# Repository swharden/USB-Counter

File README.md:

# USB Counter

This project contains the design files and notes for a USB counter. By populating one of two input paths with components this device can serve as a sensitive frequency counter (with a small-signal amplifier front-end) or a pulse counter (with a simple 50 ohm load at the front-end). Measured frequency is sent to the computer over USB, but can also be displayed on an optional 7-segment display module.

### LED Display

In addition to serial output, this counter can optionally interface a SPI-driven 7-segment display (based on a MAX7219). These display modules are about [$4 on Amazon](https://www.amazon.com/s?k=max7219+segment) and allow this counter to be used without a computer. Note that the LED display and USB output can both be used at the same time.

### USB (Serial) Output

When plugged in to a USB port the counter looks like a serial device. It continuously transmits the count (at 115200 baud) at an update rate which can be customized (commonly 1Hz, 10Hz, and 100Hz.) The output is two numbers: time (in seconds) and the count between the last update and this one. In this example it is measuring a radio frequency signal near 10.139977 MHz

### Precision Frequency Measurement

One advantage of this counter is that it is never reset. Its core is a 32-bit counter, and every gate cycle transmits the current count to the computer over USB. Because every input cycle is measured high precision measurements of frequency over long periods of time are possible. For example, 1000 repeated measurements with a 1Hz gate allows frequency measurement to a precision of 0.01 Hz.

### Internal or External Gating
The microcontroller is capable of generating gate cycles in software. Precision is limited to that of the TCXO used to clock the microcontroller (2.5 PPM). For higher-precision gating a resistor may be lifted and an external gate applied (e.g., 1PPS GPS signal).

### Design and Build Notes

* [Revision 1.0 - schematics and PCB design](/builds/1.0) - first tested 2019-07-26
* [Revision 1.1 - schematics and PCB design](/builds/1.1) - first tested 2019-08-03

### About

This project was created by [Harden Technologies, LLC](http://tech.swharden.com). To inquire about the development special features or customized versions of this hardware or software, contact the author at [SWHarden@gmail.com](mailto:swharden@gmail.com).

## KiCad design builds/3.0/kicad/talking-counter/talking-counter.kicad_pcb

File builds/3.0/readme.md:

# Talking Frequency Counter

This version of the frequency counter uses USB for power (not connectivity) and speaks frequency out loud when a button is pressed. Once finished this project will probably be moved into its own repository.

## Build Notes

* VDDIO2 should be connected to 3.3V (required bodge wire)
* Crystal pads are silly big
* Audio amplifier shutdown should be pulled LOW not HIGH
* Volume knob is wired backwards
* Rename header 3.3v to VCC
* Button is wired incorrectly (always grounded)
* Move header closer to the edge or use different system
* Don't use port C for LEDs or button

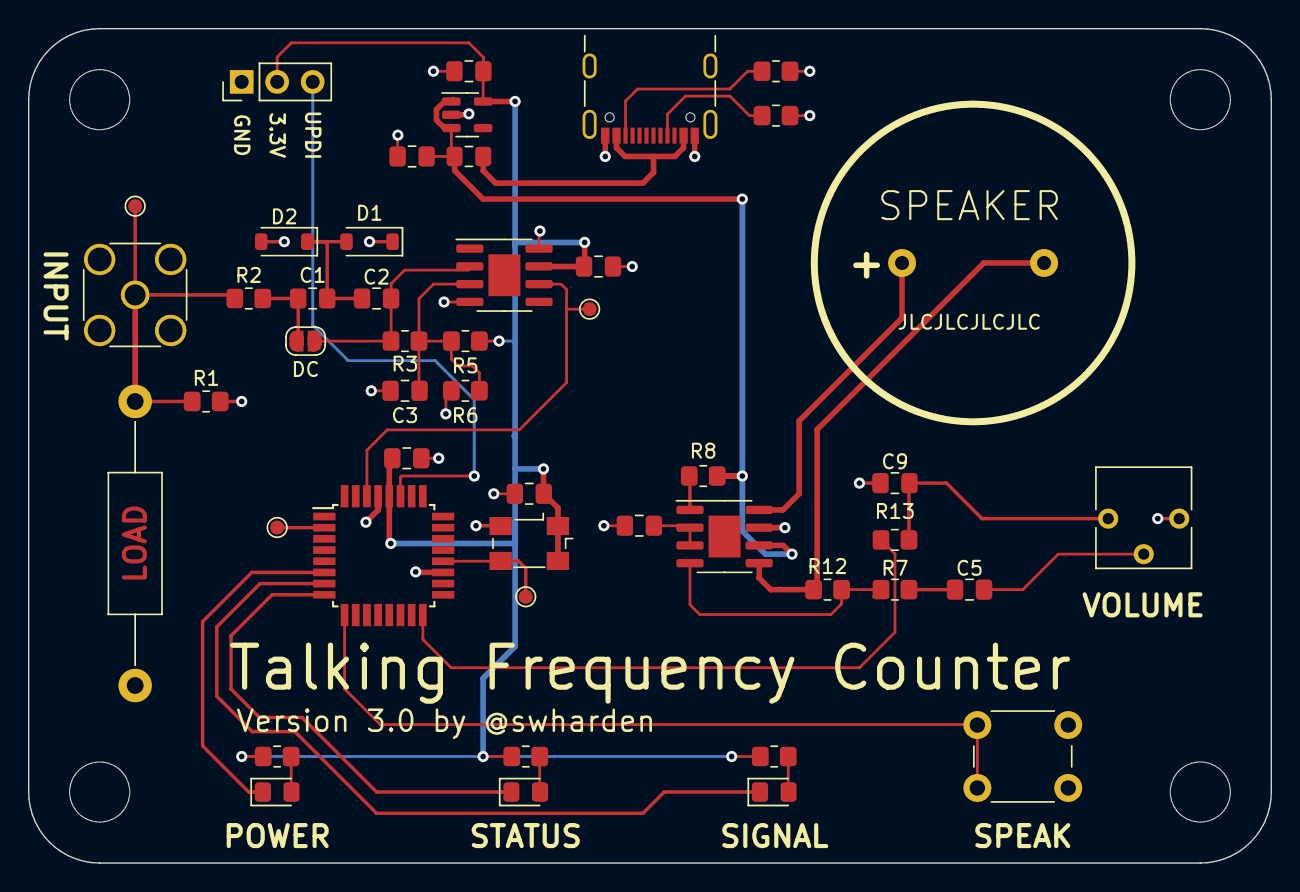
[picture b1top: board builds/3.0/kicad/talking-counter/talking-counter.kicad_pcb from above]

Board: 2 copper layers, 88.9 x 59.7 mm, 48 parts (0 on the bottom side), 31 nets.

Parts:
C1, C2, C3, C4, C5, C6, C7, C8, C9, C10, C11: .1u; C_0805_2012Metric_Pad1.18x1.45mm_HandSolder
D1, D2: D; D_SOD-123
D3: SIGNAL; LED_0805_2012Metric_Pad1.15x1.40mm_HandSolder
D4: STATUS; LED_0805_2012Metric_Pad1.15x1.40mm_HandSolder
D6: POWER; LED_0805_2012Metric_Pad1.15x1.40mm_HandSolder
FB2: Ferrite; L_0805_2012Metric_Pad1.15x1.40mm_HandSolder
IC1: TLV3501AIDR; SOIC-8-1EP_3.9x4.9mm_P1.27mm_EP2.29x3mm
IC2: LM4862MX_NOPB; SOIC-8-1EP_3.9x4.9mm_P1.27mm_EP2.29x3mm
J1: Conn_Coaxial; SMA_Amphenol_132134_Vertical
J2: PROG; PinHeader_1x03_P2.54mm_Vertical
J3: USB_C_Receptacle_PowerOnly_6P; USB_C_Receptacle_GCT_USB4105-xx-A_16P_TopMnt_Horizontal
JP1: DC_INPUT; SolderJumper-2_P1.3mm_Open_RoundedPad1.0x1.5mm
LS1: Speaker; speaker SM231508
R1, R3: 100k; R_0805_2012Metric_Pad1.20x1.40mm_HandSolder
R2, R7: 1k; R_0805_2012Metric_Pad1.20x1.40mm_HandSolder
R4, R5, R6, R8, R9, R13, R16: 10k; R_0805_2012Metric_Pad1.20x1.40mm_HandSolder
R10, R11: 5.1k; R_0805_2012Metric_Pad1.20x1.40mm_HandSolder
R12: 47k; R_0805_2012Metric_Pad1.20x1.40mm_HandSolder
RV1: R_VOL; Potentiometer_Vishay_T73YP_Vertical
R_LOAD1: 50; R_Axial_DIN0411_L9.9mm_D3.6mm_P20.32mm_Horizontal
SW1: SPEAK; SW_PUSH_6mm_H5mm
TP1: AMP_OUT; TestPoint_Pad_D1.0mm
TP2: 10MHz; TestPoint_Pad_D1.0mm
TP3: SIG_IN; TestPoint_Pad_D1.0mm
TP4: MCU_TX; TestPoint_Pad_D1.0mm
U2: AP2112K-3.3; SOT-23-5
U3: AVR64DD32; TQFP-32_7x7mm_P0.8mm
U4: FT5HV; Oscillator_SMD_Fox_FT5H_5.0x3.2mm

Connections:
+3.3V: C4.2, C7.2, C8.2, C11.2, IC1.7 (V+), J2.2, R4.2, R5.2, R9.2, R16.2, U2.5 (VOUT), U3.28 (VDD), U4.1 (VC), U4.4 (VDD)
+5V: C10.2, FB2.2, IC2.6 (VDD), R8.1, U2.1 (VIN), U2.3 (EN)
COMP_OUT: IC1.6 (OUT), TP1.1, U3.30 (PA0)
DAC: C9.2, R13.2, RV1.1
GND: C3.2, C4.1, C6.2, C7.1, C8.1, C9.1, C10.1, C11.1, D1.1 (K), D2.2 (A), IC1.4 (V-), IC1.8 (SHDN), IC2.7 (GND), J1.2 (Ext), J2.1, J3.A1, J3.A12 (GND), R1.2, R6.1, R10.2, R11.2, RV1.3, R_LOAD1.2, SW1.1, SW1.2, U2.2 (GND), U3.19 (GND), U3.29 (GND), U4.2 (GND)
LED1: D6.1 (K), U3.6 (PC0)
LED2: D3.1 (K), U3.7 (PC1)
LED3: D4.1 (K), U3.8 (PC2)
unnamed: C5.1, R7.2
unnamed: C5.2, RV1.2
unnamed: C1.1, C2.2, D1.2 (A), D2.1 (K)
unnamed: D3.2 (A), R4.1
unnamed: D4.2 (A), R9.1
unnamed: D6.2 (A), R16.1
unnamed: FB2.1, J3.A4, J3.A9 (VBUS)
unnamed: C3.1, IC1.3 (+IN), R3.1, R5.1, R6.2
unnamed: C2.1, IC1.2 (-IN), JP1.2 (B), R3.2
unnamed: C6.1, IC2.2 (BYPASS), IC2.3 (+IN)
unnamed: IC2.4 (-IN), R7.1, R12.2
unnamed: IC2.1 (SHUTDOWN), R8.2
unnamed: IC2.5 (VO1), LS1.2, R12.1
unnamed: IC2.8 (VO2), LS1.1
unnamed: J1.1 (In), R1.1, R2.1, R_LOAD1.1, TP3.1
unnamed: J2.3, U3.27 (UPDI)
unnamed: J3.A5 (CC1), R11.1
unnamed: J3.B5 (CC2), R10.1
unnamed: C1.2, JP1.1 (A), R2.2
unnamed: TP4.1, U3.2 (PA4)
unnamed: SW1.1, SW1.2, U3.9 (PC3)
unnamed: R13.1, U3.16 (PD6)
unnamed: TP2.1, U3.20 (XTAL32K1/PF0), U4.3 (OUT)

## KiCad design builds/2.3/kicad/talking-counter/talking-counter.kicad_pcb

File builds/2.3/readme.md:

# Talking Frequency Counter

This folder contains design notes for a ***talking frequency counter*** designed to help visually impaired radio operators to know what frequency they are transmitting on by speaking the frequency out loud when a button is pressed. This design uses a high-speed analog comparator to amplify signals on the frontend, measures them directly with a microcontroller, sends that data to a PC using a USB serial adapter, and also says the frequency out loud using a speaker.

> **⚠️ WARNING:** This is a work in progress. This board design has some errors which will be corrected in a future build.

## Components
* **AP2112K-3.3TRG1** 600 mA 3.3V LDO regulator ([$0.35 from Mouser](https://www.mouser.com/ProductDetail/Diodes-Incorporated/AP2112K-3.3TRG1?qs=x6A8l6qLYDDPYHosCdzh%2FA%3D%3D))
* **AVR64DD32** 8-bit microcontroller ([$1.51 on Mouser](https://www.mouser.com/ProductDetail/Microchip-Technology/AVR64DD32-I-PT?qs=tlsG%2FOw5FFjuwvYsegdIqg%3D%3D))
* **Oscillator** 10 MHz oscillator, 3.3V, ±2.5 ppm ([$1.89 on Mouser](https://www.mouser.com/ProductDetail/ECS/ECS-TXO-2016-33-100-TR?qs=PzGy0jfpSMvd6OxkHIkpfg%3D%3D))
* **TLV3501** high speed analog comparator ([$3.06 on Mouser](https://www.mouser.com/ProductDetail/Texas-Instruments/TLV3501AIDR?qs=m96fseALk3U7ir0PfDMQ%252BA%3D%3D))
* **LM4862** audio amplifier ([$1.21 on Mouser](https://www.mouser.com/ProductDetail/Texas-Instruments/LM4862MX-NOPB?qs=QbsRYf82W3HZp12WHQE14A%3D%3D))
* **FT231** USB Serial Adapter ([$2.33 on Mouser](https://www.mouser.com/ProductDetail/FTDI/FT231XS-R?qs=Gp1Yz1mis3WduRPsgrTbtg%3D%3D))
* **Diode** 100V 4A 4ns recovery ([$0.13 on Mouser](https://www.mouser.com/ProductDetail/Panjit/1N4148W_R1_00001?qs=sPbYRqrBIVnqVztCqPNVrw%3D%3D))
* **Speaker** 8Ω 300 mW ([$2.09 on Mouser](https://www.mouser.com/ProductDetail/DB-Unlimited/SM231508-1?qs=t9M3m0YJX4Ng139DBuQXjw%3D%3D))
* **USB Connector** type B micro ([$0.46 on Mouser](https://www.mouser.com/ProductDetail/Amphenol-FCI/10118193-0001LF?qs=Ywefl8B65e63Nsqd%252B8HZaQ%3D%3D))
* **USB Connector (next time)** use USBC ([$0.80 on Mouser](https://www.mouser.com/ProductDetail/GCT/USB4105-GF-A?qs=KUoIvG%2F9IlY%2FMLlBMpStpA%3D%3D))
* **0802 Components** are purchased in bulk and essentially free
* **Bumpers** for raising the PCB ([Bumpon SJ5076 from eBay](https://www.mouser.com/datasheet/2/1/Bumpon%20Molded%20Shapes%20Colored%20and%20Clear%20Series%20TDS-845047.pdf))

_Approximately $13 total_

## Schematic

## Preview Render

## Resources

* [100 MHz frequency counter](https://www.electronics-lab.com/project/100mhz-frequency-counter-with-pic16f628a-2/) (designed by Hristo) uses the TLV3501 for its frontend

* [Frequency Measurement with Modern AVR Microcontrollers](https://swharden.com/blog/2023-08-31-avr-dd-frequency-counter/)

* [Play Audio from SPI Flash with a Microcontroller](https://swharden.com/blog/2023-08-26-spi-flash-audio/)

* [Speaking Numbers with a Microcontroller](https://swharden.com/blog/2023-08-19-speaking-microcontroller/)

## Photo

Oof that's a lot of bodges

## Notes During the Build
* PCB edges should be rounded
* Green LEDs should have 47k resistors (not 10k)
* USB lines are incorrect. They should be:
  * 1. VCC
  * 2. ?
  * 3. ?
  * 4. ID (nc)
  * 5. GND
* Need to order more .1 µF caps
* Speaker holes should be bigger
* Volume knob holes should be bigger
* Volume knob polarity should be reversed
* Label programmer pins
* Amplifier shutdown pin should be grounded (not tied to VCC)
* Amplifier resistors should be R12=47k and R7=1k
* The button is wired wrong. Bottom right pin should be grounded.
* Test points should be labeled.
* Add a test point for comparator input and output.
* Ground screw holes.
* Omit RX led (only TX needed)
* Use smaller volume knob and move it away from the button
* Speaker hides power LED
* Move prog header to edge of board
* The load resistor "optional" label is floating beneath the RX/TX leds
* Omit C14 and replace R17 with a 1k resistor
* Use green LEDs everywhere
* Fix the double-press issue
* RF front-end: use a dual diode
* RF front-end: don't tap COMP_OUT with a LED (do that in software)
* Just add TX test pad (not FTDI chip)
* Load comparator output
* Jumper to bypass AC coupling on input

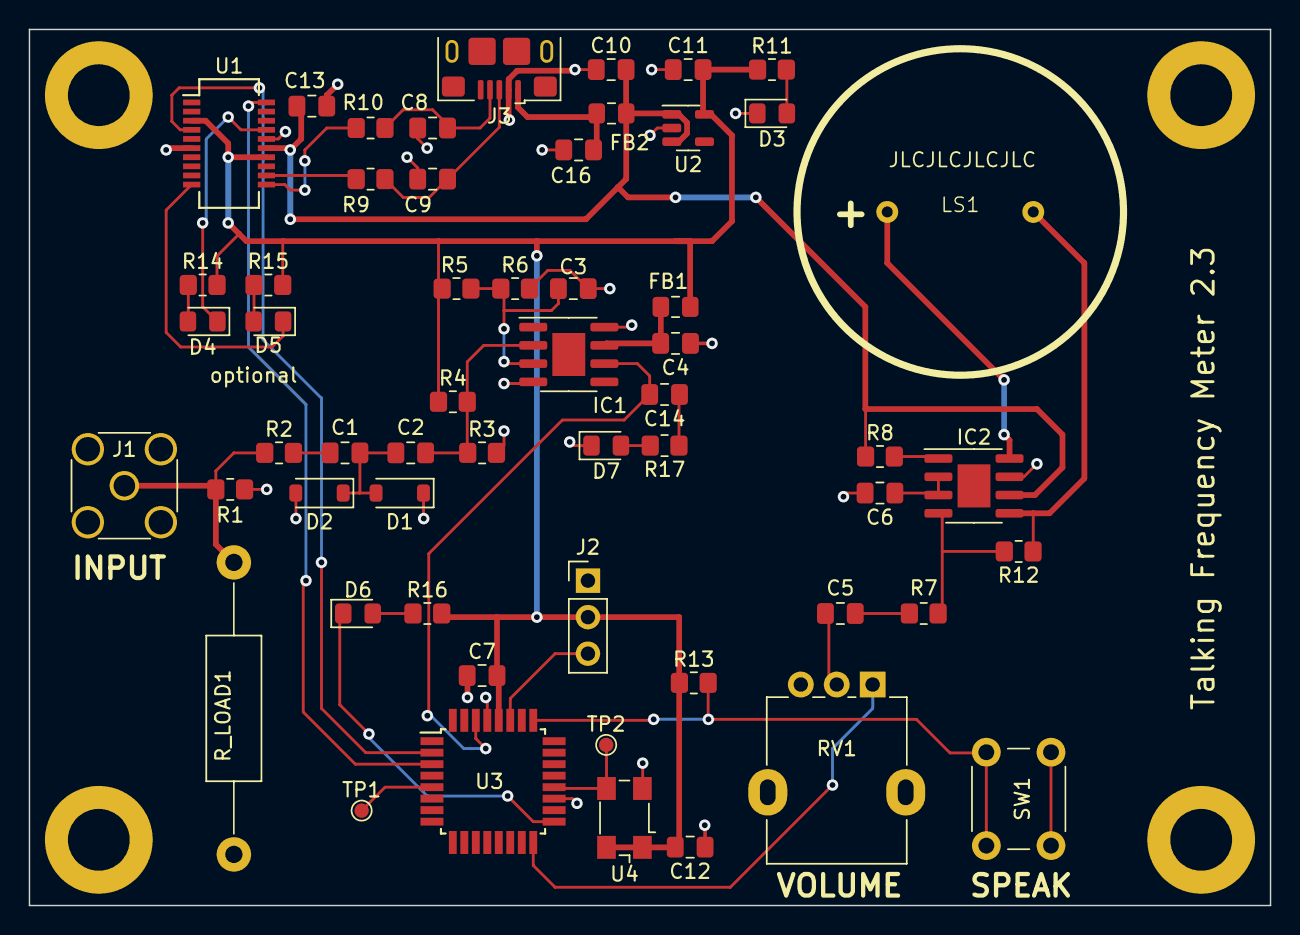
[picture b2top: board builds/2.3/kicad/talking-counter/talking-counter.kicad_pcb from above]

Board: 2 copper layers, 86.4 x 61.0 mm, 60 parts (0 on the bottom side), 38 nets.

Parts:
C1, C2, C3, C4, C5, C6, C7, C10, C11, C12, C13, C14, C16: .1u; C_0805_2012Metric_Pad1.18x1.45mm_HandSolder
C8, C9: 47p; C_0805_2012Metric_Pad1.18x1.45mm_HandSolder
D1, D2: D; D_SOD-123
D3: LED_PWR; LED_0805_2012Metric_Pad1.15x1.40mm_HandSolder
D4: RX_LED; LED_0805_2012Metric_Pad1.15x1.40mm_HandSolder
D5: TX_LED; LED_0805_2012Metric_Pad1.15x1.40mm_HandSolder
D6: LED_STATUS; LED_0805_2012Metric_Pad1.15x1.40mm_HandSolder
D7: LED_SIG; LED_0805_2012Metric_Pad1.15x1.40mm_HandSolder
FB1, FB2: Ferrite; L_0805_2012Metric_Pad1.15x1.40mm_HandSolder
H1, H2, H3, H4: MountingHole; MountingHole_4.3mm_M4_DIN965_Pad
IC1: TLV3501AIDR; SOIC-8-1EP_3.9x4.9mm_P1.27mm_EP2.29x3mm
IC2: LM4862MX_NOPB; SOIC-8-1EP_3.9x4.9mm_P1.27mm_EP2.29x3mm
J1: Conn_Coaxial; SMA_Amphenol_132134_Vertical
J2: PROG; PinHeader_1x03_P2.54mm_Vertical
J3: UJ2-MIBH-G-SMT-TR; USB_Micro-B_Amphenol_10118193-0001LF_Horizontal
LS1: Speaker; speaker SM231508
R1: 100k; R_0805_2012Metric_Pad1.20x1.40mm_HandSolder
R2: 1k; R_0805_2012Metric_Pad1.20x1.40mm_HandSolder
R3, R4, R5, R6, R7, R8, R11, R12, R13, R14, R15, R16, R17: 10k; R_0805_2012Metric_Pad1.20x1.40mm_HandSolder
R9, R10: 27; R_0805_2012Metric_Pad1.20x1.40mm_HandSolder
RV1: R_VOL; Potentiometer_Alpha_RD901F-40-00D_Single_Vertical
R_LOAD1: 50; R_Axial_DIN0411_L9.9mm_D3.6mm_P20.32mm_Horizontal
SW1: SW_MEC_5E; SW_PUSH_6mm_H5mm
TP1: CKOUT; TestPoint_Pad_D1.0mm
TP2: 10MHz; TestPoint_Pad_D1.0mm
U1: FT231XS; SSOP-20_3.9x8.7mm_P0.635mm
U2: AP2112K-3.3; SOT-23-5
U3: AVR64DD32; TQFP-32_7x7mm_P0.8mm
U4: FT5HV; Oscillator_SMD_Fox_FT5H_5.0x3.2mm

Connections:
+5V: C10.2, C13.2, FB2.1, IC2.6 (VDD), R8.1, U1.15 (VCC), U2.1 (VIN), U2.3 (EN)
COMP_OUT: C14.2, IC1.6 (OUT), U3.30 (PA0)
DAC: RV1.1, U3.16 (PD6)
GND: C3.2, C4.1, C6.2, C7.1, C8.2, C9.1, C10.1, C11.1, C12.1, C13.1, C16.1, D1.1 (K), D2.2 (A), D3.1 (K), D7.1 (K), IC1.4 (V-), IC1.8 (SHDN), IC2.7 (GND), J1.2 (Ext), J2.1, J3.2, R1.2, R3.2, R6.1, RV1.3, R_LOAD1.2, U1.6 (GND), U1.16 (GND), U2.2 (GND), U3.19 (GND), U3.29 (GND), U4.2 (GND)
MCU_RX: U1.20 (TXD), U3.3 (PA5)
MCU_TX: U1.4 (RXD), U3.2 (PA4)
unnamed: C1.2, R2.2
unnamed: C5.1, R7.2
unnamed: C5.2, RV1.2
unnamed: C8.1, J3.4, R10.2
unnamed: C9.2, J3.3, R9.1
unnamed: C14.1, R17.1
unnamed: C16.2, FB2.2, J3.1
unnamed: C1.1, C2.2, D1.2 (A), D2.1 (K)
unnamed: D3.2 (A), R11.2
unnamed: D4.2 (A), R14.1
unnamed: D4.1 (K), U1.17 (CBUS1)
unnamed: D5.2 (A), R15.1
unnamed: D5.1 (K), U1.10 (CBUS2)
unnamed: D6.2 (A), R16.1
unnamed: D6.1 (K), U3.17 (VREFA/PD7)
unnamed: D7.2 (A), R17.2
unnamed: C3.1, IC1.3 (+IN), R5.1, R6.2
unnamed: C2.1, IC1.2 (-IN), R3.1, R4.2
unnamed: C4.2, FB1.2, IC1.7 (V+)
unnamed: C6.1, IC2.2 (BYPASS), IC2.3 (+IN)
unnamed: IC2.4 (-IN), R7.1, R12.2
unnamed: IC2.1 (SHUTDOWN), R8.2
unnamed: IC2.5 (VO1), LS1.2, R12.1
unnamed: IC2.8 (VO2), LS1.1
unnamed: J1.1 (In), R1.1, R2.1, R_LOAD1.1
unnamed: J2.3, U3.27 (UPDI)
unnamed: R9.2, U1.12 (USBDM)
unnamed: R10.1, U1.11 (USBDP)
unnamed: TP1.1, U3.5 (PA7)
unnamed: R13.2, SW1.2, U3.25 (PF5)
unnamed: TP2.1, U3.20 (XTAL32K1/PF0), U4.3 (OUT)
VCC: C7.2, C11.2, C12.2, FB1.1, J2.2, R4.1, R5.2, R11.1, R13.1, R14.2, R15.2, R16.2, U1.3 (VCCIO), U1.14 (~RESET), U2.5 (VOUT), U3.28 (VDD), U4.1 (VC), U4.4 (VDD)

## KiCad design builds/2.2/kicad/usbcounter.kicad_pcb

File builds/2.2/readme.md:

# Version 2.2

## Thoughts

* Make an RF amplifier board separately (perhaps with prescaler)
* Input should be 0-5V TTL
* What makes this unique is no-cycle-lost counting
* Ability to accept a 10 MHz lab reference clock is also a big win

## Build notes
* Red and blue LEDs need 1K resistors
* Green LEDs need 47k resistors
* Capacitors on USB line should be 47pF
* LJCPCB blue silkscreen is ugly and doesn't hold up to heat as well as green
* For the crystal oscillator indicate where the dot goes
* It's annoying to keep rotating the board when hand assembling so lay-out passives horizontally
* Move the board ID under one of the ICs
* Consider horizontally mounted headers and SMA connector to facilitate stacking
* Clamp diodes should be downstream of the input decoupling decapacitors
* External 10MHz clock is going into the wrong pin (32 kHz clock). Clock should go to PA0/PA1 and USART use alternate pins PD4/PD5

## Schematic

## Alternative Frontend Designs

### TLV3501 RF Comparator

### OPA356 RF Opamp

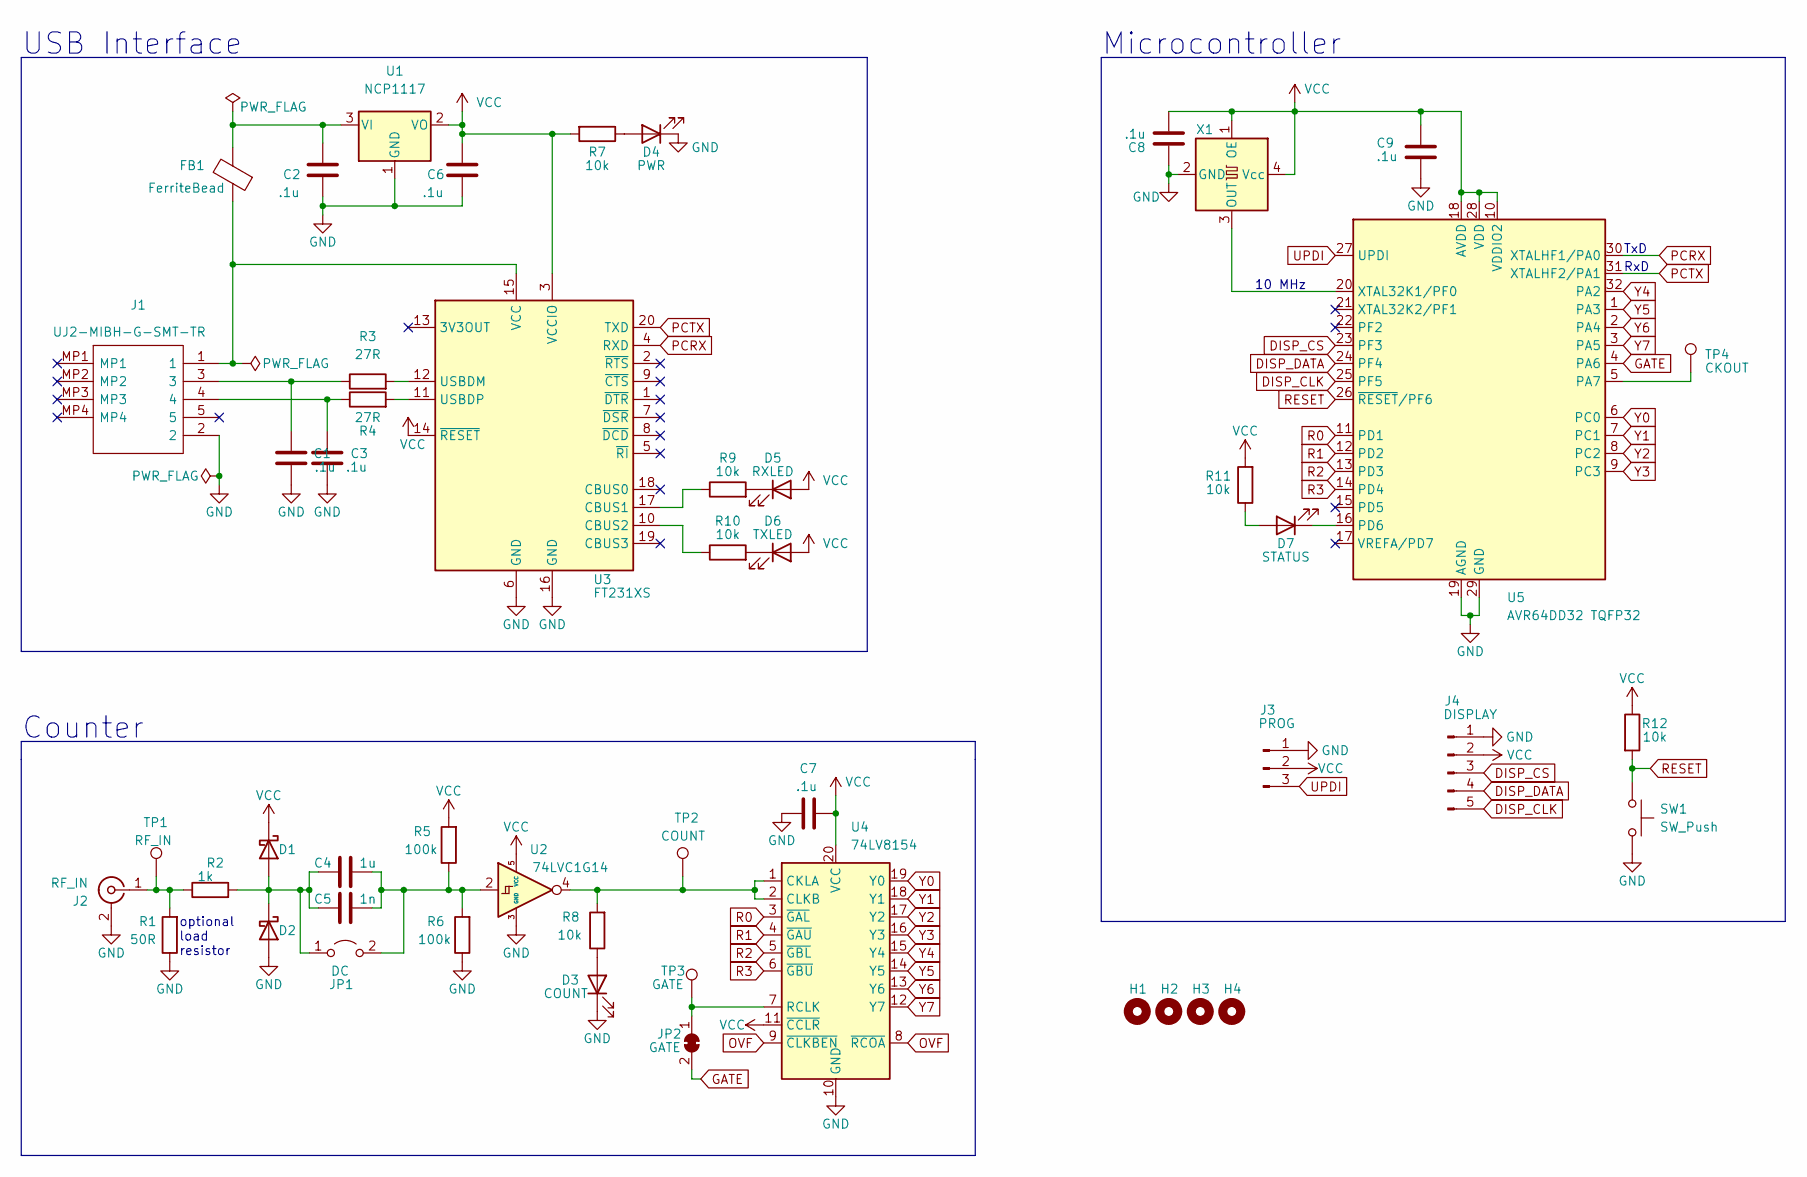
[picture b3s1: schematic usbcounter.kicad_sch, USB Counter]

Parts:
C1, C2, C3, C6, C7, C8, C9: .1u; C_0805_2012Metric_Pad1.18x1.45mm_HandSolder
C4: 1u; C_0805_2012Metric_Pad1.18x1.45mm_HandSolder
C5: 1n; C_0805_2012Metric_Pad1.18x1.45mm_HandSolder
D1, D2: D; LED_0805_2012Metric_Pad1.15x1.40mm_HandSolder
D3: COUNT; LED_0805_2012Metric_Pad1.15x1.40mm_HandSolder
D4: PWR; LED_0805_2012Metric_Pad1.15x1.40mm_HandSolder
D5: RXLED; LED_0805_2012Metric_Pad1.15x1.40mm_HandSolder
D6: TXLED; LED_0805_2012Metric_Pad1.15x1.40mm_HandSolder
D7: STATUS; LED_0805_2012Metric_Pad1.15x1.40mm_HandSolder
FB1: FerriteBead; L_0805_2012Metric_Pad1.15x1.40mm_HandSolder
H1, H2, H3, H4: MountingHole; MountingHole_4.3mm_M4_Pad
J1: UJ2-MIBH-G-SMT-TR; UJ2MIBHGSMTTR; Mouser Part Number 490-UJ2-MIBH-G-SMTTR
J2: RF_IN; SMA_Amphenol_901-144_Vertical
J3: PROG; PinHeader_1x03_P2.54mm_Vertical
J4: DISPLAY; PinHeader_1x05_P2.54mm_Vertical
JP1: DC; SolderJumper-2_P1.3mm_Open_RoundedPad1.0x1.5mm
JP2: GATE; SolderJumper-2_P1.3mm_Bridged_RoundedPad1.0x1.5mm
R1: 50R; R_Axial_DIN0207_L6.3mm_D2.5mm_P7.62mm_Horizontal
R2: 1k; R_0805_2012Metric_Pad1.20x1.40mm_HandSolder
R3, R4: 27R; R_0805_2012Metric_Pad1.20x1.40mm_HandSolder
R5, R6: 100k; R_0805_2012Metric_Pad1.20x1.40mm_HandSolder
R7, R8, R9, R10, R11, R12: 10k; R_0805_2012Metric_Pad1.20x1.40mm_HandSolder
SW1: SW_Push; SW_SPST_TL3342
TP1: RF_IN; TestPoint_Pad_D2.0mm
TP2: COUNT; TestPoint_Pad_D2.0mm
TP3: GATE; TestPoint_Pad_D2.0mm
TP4: CKOUT; TestPoint_Pad_D2.0mm
U1: NCP1117; SOT-223-3_TabPin2
U2: 74LVC1G14; SOT-23-5
U3: FT231XS; SSOP-20_3.9x8.7mm_P0.635mm
U4: 74LV8154; TSSOP-20_4.4x6.5mm_P0.65mm
U5: AVR64DD32 TQFP32; TQFP-32_7x7mm_P0.8mm
X1: TCXO; Oscillator_SMD_SeikoEpson_SG8002CE-4Pin_3.2x2.5mm

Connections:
DISP_CLK: J4.5, U5.25 (PF5)
DISP_CS: J4.3, U5.23 (PF3)
DISP_DATA: J4.4, U5.24 (PF4)
GATE: JP2.2 (B), U5.4 (PA6)
GND: C1.1, C2.1, C3.1, C6.1, C7.1, C8.2, C9.1, D2.2 (A), D3.1 (K), D4.1 (K), J1.2, J2.2 (Ext), J3.1, J4.1, R1.1, R6.1, SW1.2, U1.1 (GND), U2.3 (GND), U3.6 (GND), U3.16 (GND), U4.10 (GND), U5.19 (AGND), U5.29 (GND), X1.2 (GND)
unnamed: C1.2, J1.3, R3.1
unnamed: C2.2, FB1.2, U1.3 (VI)
unnamed: C3.2, J1.4, R4.1
unnamed: C4.1, C5.1, D1.2 (A), D2.1 (K), JP1.1 (A), R2.2
unnamed: C4.2, C5.2, JP1.2 (B), R5.1, R6.2, U2.2
unnamed: D3.2 (A), R8.1
unnamed: D4.2 (A), R7.1
unnamed: D5.1 (K), R9.2
unnamed: D6.1 (K), R10.2
unnamed: FB1.1, J1.1, U3.15 (VCC)
unnamed: J2.1 (In), R1.2, R2.1, TP1.1
unnamed: JP2.1 (A), TP3.1, U4.7 (RCLK)
unnamed: R3.2, U3.12 (USBDM)
unnamed: R4.2, U3.11 (USBDP)
unnamed: R8.2, TP2.1, U2.4, U4.1 (CKLA), U4.2 (CLKB)
unnamed: R9.1, U3.17 (CBUS1)
unnamed: R10.1, U3.10 (CBUS2)
unnamed: D7.2 (A), R11.1
unnamed: TP4.1, U5.5 (PA7)
unnamed: D7.1 (K), U5.16 (PD6)
unnamed: U5.20 (XTAL32K1/PF0), X1.3 (OUT)
OVF: U4.8 (~RCOA), U4.9 (~CLKBEN)
PCRX: U3.4 (RXD), U5.30 (XTALHF1/PA0)
PCTX: U3.20 (TXD), U5.31 (XTALHF2/PA1)
R0: U4.3 (~GAL), U5.11 (PD1)
R1: U4.4 (~GAU), U5.12 (PD2)
R2: U4.5 (~GBL), U5.13 (PD3)
R3: U4.6 (~GBU), U5.14 (PD4)
RESET: R12.2, SW1.1, U5.26 (~RESET/PF6)
UPDI: J3.3, U5.27 (UPDI)
VCC: C6.2, C7.2, C8.1, C9.2, D1.1 (K), D5.2 (A), D6.2 (A), J3.2, J4.2, R5.2, R7.2, R11.2, R12.1, U1.2 (VO), U2.5 (VCC), U3.3 (VCCIO), U3.14 (~RESET), U4.11 (~CCLR), U4.20 (VCC), U5.10 (VDDIO2), U5.18 (AVDD), U5.28 (VDD), X1.1 (OE), X1.4 (Vcc)
Y0: U4.19 (Y0), U5.6 (PC0)
Y1: U4.18 (Y1), U5.7 (PC1)
Y2: U4.17 (Y2), U5.8 (PC2)
Y3: U4.16 (Y3), U5.9 (PC3)
Y4: U4.15 (Y4), U5.32 (PA2)
Y5: U4.14 (Y5), U5.1 (PA3)
Y6: U4.13 (Y6), U5.2 (PA4)
Y7: U4.12 (Y7), U5.3 (PA5)

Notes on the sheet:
USB Interface
TxD
10 MHz
Microcontroller
RxD
Counter
optional load resistor

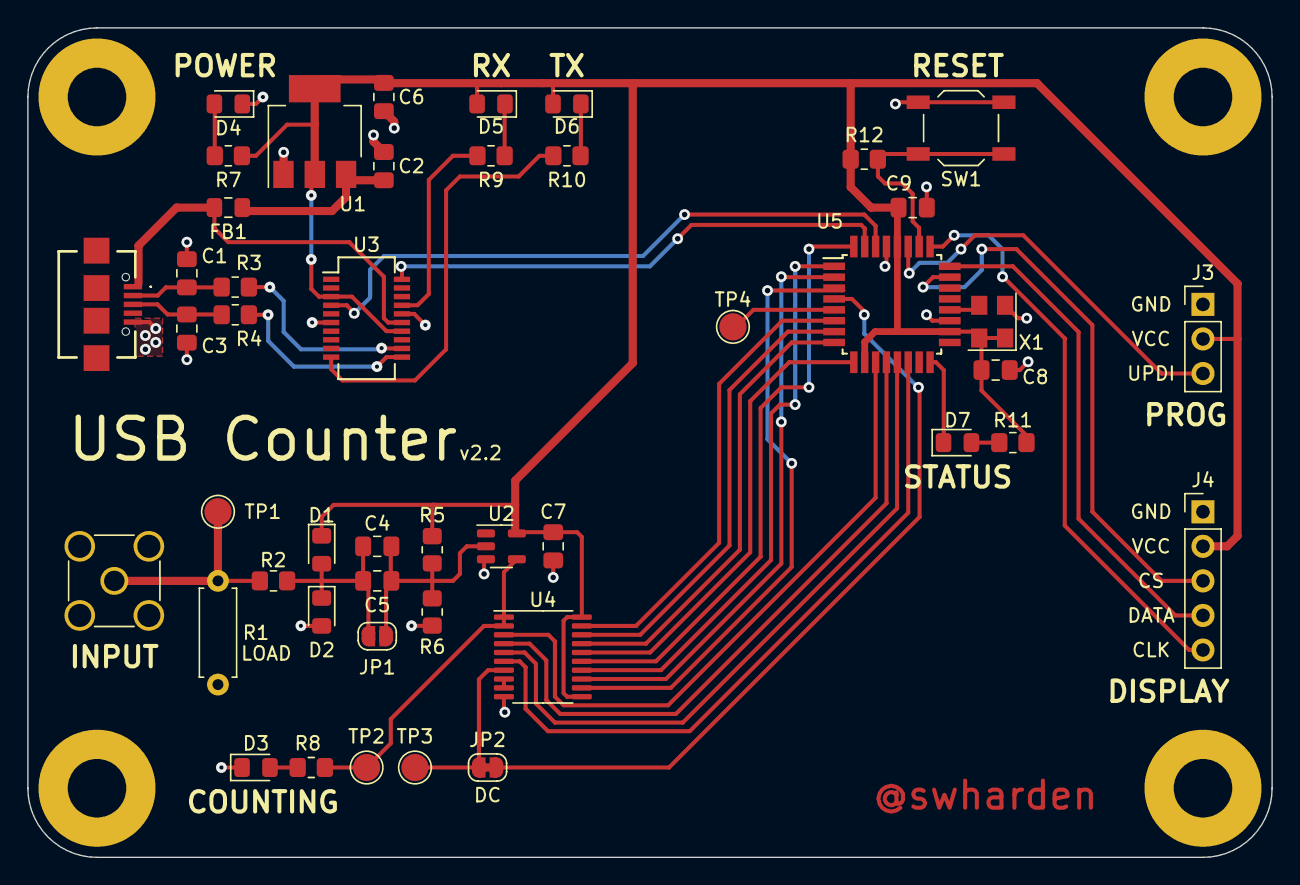
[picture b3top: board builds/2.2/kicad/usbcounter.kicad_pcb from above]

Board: 2 copper layers, 91.4 x 61.0 mm, 50 parts (0 on the bottom side), 44 nets.

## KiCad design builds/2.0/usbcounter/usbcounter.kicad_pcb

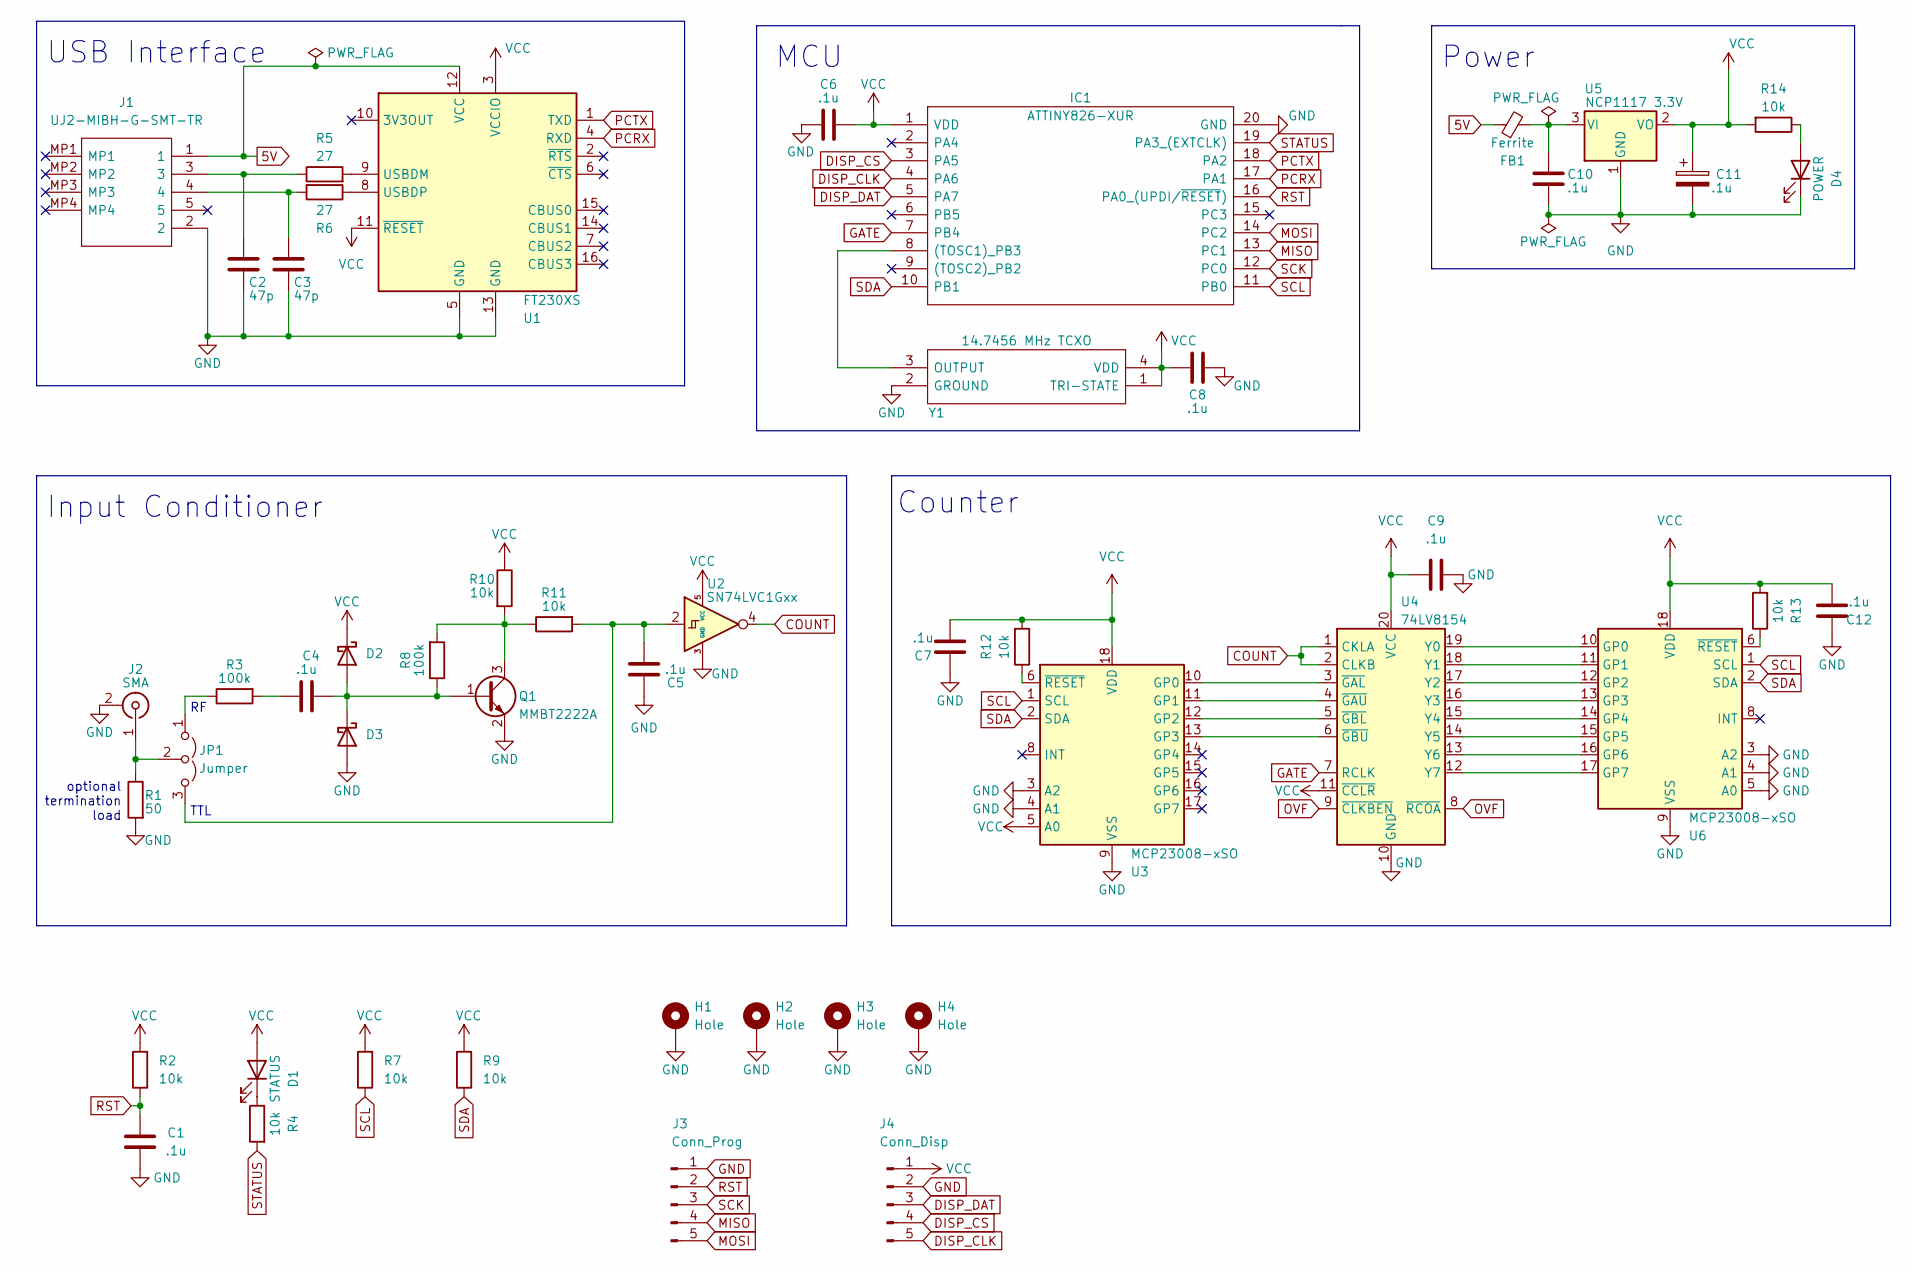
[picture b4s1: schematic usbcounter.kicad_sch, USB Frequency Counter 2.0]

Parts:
C1, C4, C5, C6, C7, C8, C9, C10, C12: .1u; C_0805_2012Metric_Pad1.18x1.45mm_HandSolder
C2, C3: 47p; C_0805_2012Metric_Pad1.18x1.45mm_HandSolder
C11: .1u; CP_EIA-2012-15_AVX-P_Pad1.30x1.05mm_HandSolder
D1: STATUS; LED_0805_2012Metric_Pad1.15x1.40mm_HandSolder
D2, D3: D; D_SOD-323_HandSoldering
D4: POWER; LED_0805_2012Metric_Pad1.15x1.40mm_HandSolder
FB1: Ferrite; L_0805_2012Metric_Pad1.15x1.40mm_HandSolder
H1, H2, H3, H4: Hole; MountingHole_2.2mm_M2_DIN965_Pad
IC1: ATTINY826-XUR; SOP65P780X200-20N; Mouser Part Number 579-ATTINY826-XUR
J1: UJ2-MIBH-G-SMT-TR; UJ2MIBHGSMTTR; Mouser Part Number 490-UJ2-MIBH-G-SMTTR
J2: SMA; SMA_Amphenol_901-144_Vertical
J3: Conn_Prog; PinHeader_1x05_P2.54mm_Vertical
J4: Conn_Disp; PinHeader_1x05_P2.54mm_Vertical
JP1: Jumper; PinHeader_1x03_P2.54mm_Vertical
Q1: MMBT2222A; SOT-23
R1: 50; R_Axial_DIN0207_L6.3mm_D2.5mm_P10.16mm_Horizontal
R2, R4, R7, R9, R10, R11, R12, R13, R14: 10k; R_0805_2012Metric_Pad1.20x1.40mm_HandSolder
R3, R8: 100k; R_0805_2012Metric_Pad1.20x1.40mm_HandSolder
R5, R6: 27; R_0805_2012Metric_Pad1.20x1.40mm_HandSolder
U1: FT230XS; SSOP-16_3.9x4.9mm_P0.635mm
U2: SN74LVC1Gxx; SOT-23-5
U3, U6: MCP23008-xSO; SOIC-18W_7.5x11.6mm_P1.27mm
U4: 74LV8154; TSSOP-20_4.4x6.5mm_P0.65mm
U5: NCP1117 3.3V; SOT-223-3_TabPin2
Y1: 14.7456 MHz TCXO; ECSTXO3225MV1474TR; Mouser Part Number 520-TXO-3225MV-1474T

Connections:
5V: FB1.1, J1.1, U1.12 (VCC)
COUNT: U2.4, U4.1 (CKLA), U4.2 (CLKB)
DISP_CLK: IC1.4 (PA6), J4.5
DISP_CS: IC1.3 (PA5), J4.4
DISP_DAT: IC1.5 (PA7), J4.3
GATE: IC1.7 (PB4), U4.7 (RCLK)
GND: C1.2, C2.1, C3.1, C5.1, C6.2, C7.1, C8.1, C9.1, C10.2, C11.2, C12.1, D3.2 (A), D4.1 (K), H1.1, H2.1, H3.1, H4.1, IC1.20 (GND), J1.2, J2.2 (Ext), J3.1, J4.2, Q1.2 (E), R1.2, U1.5 (GND), U1.13 (GND), U2.3 (GND), U3.3 (A2), U3.4 (A1), U3.9 (VSS), U4.10 (GND), U5.1 (GND), U6.3 (A2), U6.4 (A1), U6.5 (A0), U6.9 (VSS), Y1.2 (GROUND)
MISO: IC1.13 (PC1), J3.4
MOSI: IC1.14 (PC2), J3.5
unnamed: C2.2, J1.3, R5.1
unnamed: C3.2, J1.4, R6.2
unnamed: C4.1, D2.2 (A), D3.1 (K), Q1.1 (B), R8.1
unnamed: C4.2, R3.2
unnamed: C5.2, JP1.3 (B), R11.2, U2.2
unnamed: C10.1, FB1.2, U5.3 (VI)
unnamed: D1.1 (K), R4.1
unnamed: D4.2 (A), R14.1
unnamed: IC1.8 ((TOSC1)_PB3), Y1.3 (OUTPUT)
unnamed: J2.1 (In), JP1.2 (C), R1.1
unnamed: JP1.1 (A), R3.1
unnamed: Q1.3 (C), R8.2, R10.2, R11.1
unnamed: R5.2, U1.9 (USBDM)
unnamed: R6.1, U1.8 (USBDP)
unnamed: R12.1, U3.6 (~RESET)
unnamed: R13.1, U6.6 (~RESET)
unnamed: U3.10 (GP0), U4.3 (~GAL)
unnamed: U3.11 (GP1), U4.4 (~GAU)
unnamed: U3.12 (GP2), U4.5 (~GBL)
unnamed: U3.13 (GP3), U4.6 (~GBU)
unnamed: U4.12 (Y7), U6.17 (GP7)
unnamed: U4.13 (Y6), U6.16 (GP6)
unnamed: U4.14 (Y5), U6.15 (GP5)
unnamed: U4.15 (Y4), U6.14 (GP4)
unnamed: U4.16 (Y3), U6.13 (GP3)
unnamed: U4.17 (Y2), U6.12 (GP2)
unnamed: U4.18 (Y1), U6.11 (GP1)
unnamed: U4.19 (Y0), U6.10 (GP0)
OVF: U4.8 (~RCOA), U4.9 (~CLKBEN)
PCRX: IC1.17 (PA1), U1.4 (RXD)
PCTX: IC1.18 (PA2), U1.1 (TXD)
RST: C1.1, IC1.16 (PA0_(UPDI/~RESET)), J3.2, R2.1
SCK: IC1.12 (PC0), J3.3
SCL: IC1.11 (PB0), R7.1, U3.1 (SCL), U6.1 (SCL)
SDA: IC1.10 (PB1), R9.1, U3.2 (SDA), U6.2 (SDA)
STATUS: IC1.19 (PA3_(EXTCLK)), R4.2
VCC: C6.1, C7.2, C8.2, C9.2, C11.1, C12.2, D1.2 (A), D2.1 (K), IC1.1 (VDD), J4.1, R2.2, R7.2, R9.2, R10.1, R12.2, R13.2, R14.2, U1.3 (VCCIO), U1.11 (~RESET), U2.5 (VCC), U3.5 (A0), U3.18 (VDD), U4.11 (~CCLR), U4.20 (VCC), U5.2 (VO), U6.18 (VDD), Y1.1 (TRI-STATE), Y1.4 (VDD)

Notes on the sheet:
USB Interface
MCU
Input Conditioner
Power
Counter
TTL
optional termination load

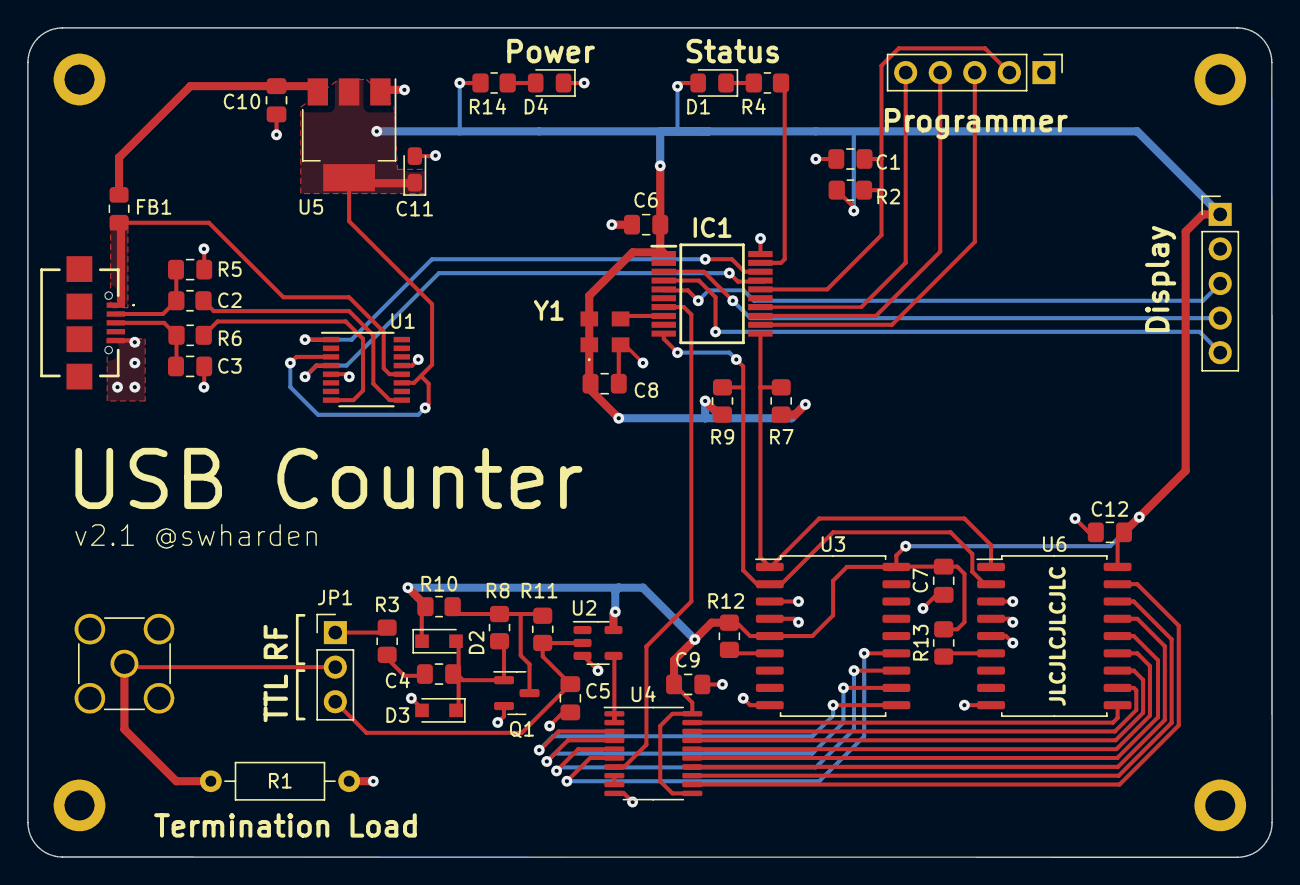
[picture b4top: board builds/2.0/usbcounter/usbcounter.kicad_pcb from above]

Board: 2 copper layers, 91.4 x 60.9 mm, 49 parts (0 on the bottom side), 46 nets.
